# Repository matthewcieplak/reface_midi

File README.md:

# reface_midi
A patch change storage box for the Yamaha Reface CS

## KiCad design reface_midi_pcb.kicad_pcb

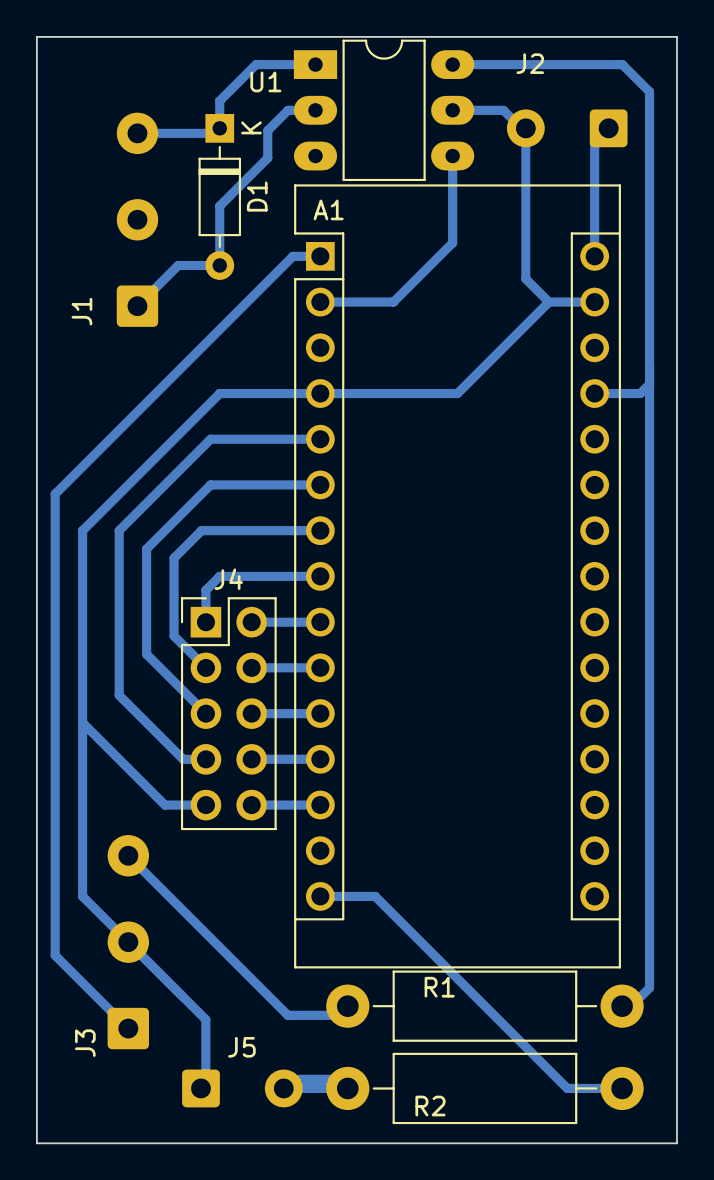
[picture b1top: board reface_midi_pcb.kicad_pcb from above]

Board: 2 copper layers, 35.6 x 61.5 mm, 10 parts (0 on the bottom side), 19 nets.

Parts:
A1: Arduino_Nano_v2.x; Arduino_Nano
D1: 1N4148; D_DO-35_SOD27_P7.62mm_Horizontal
J1: MIDI INPUT; SolderWire-0.5sqmm_1x03_P4.8mm_D0.9mm_OD2.3mm
J2: 9V IN; SolderWire-0.5sqmm_1x02_P4.6mm_D0.9mm_OD2.1mm
J3: MIDI OUTPUT; SolderWire-0.5sqmm_1x03_P4.8mm_D0.9mm_OD2.3mm
J4: Conn_02x05_Odd_Even; PinHeader_2x05_P2.54mm_Vertical
J5: LED; SolderWire-0.5sqmm_1x02_P4.6mm_D0.9mm_OD2.1mm
R1: 220; R_Axial_DIN0411_L9.9mm_D3.6mm_P15.24mm_Horizontal
R2: 500; R_Axial_DIN0411_L9.9mm_D3.6mm_P15.24mm_Horizontal
U1: H11L1; DIP-6_W7.62mm_LongPads

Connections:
GND: A1.4 (GND), A1.29 (GND), J2.2, J3.2, J4.9, J5.1, U1.5
unnamed: A1.1 (D1/TX), J3.1
unnamed: A1.2 (D0/RX), U1.4
unnamed: A1.5 (D2), J4.7
unnamed: A1.6 (D3), J4.5
unnamed: A1.7 (D4), J4.3
unnamed: A1.8 (D5), J4.1
unnamed: A1.9 (D6), J4.2
unnamed: A1.10 (D7), J4.4
unnamed: A1.11 (D8), J4.6
unnamed: A1.12 (D9), J4.8
unnamed: A1.13 (D10), J4.10
unnamed: A1.15 (D12), R2.2
unnamed: A1.27 (+5V), R1.2, U1.6
unnamed: A1.30 (VIN), J2.1
unnamed: D1.1 (K), J1.3, U1.1
unnamed: D1.2 (A), J1.1, U1.2
unnamed: J3.3, R1.1
unnamed: J5.2, R2.1
